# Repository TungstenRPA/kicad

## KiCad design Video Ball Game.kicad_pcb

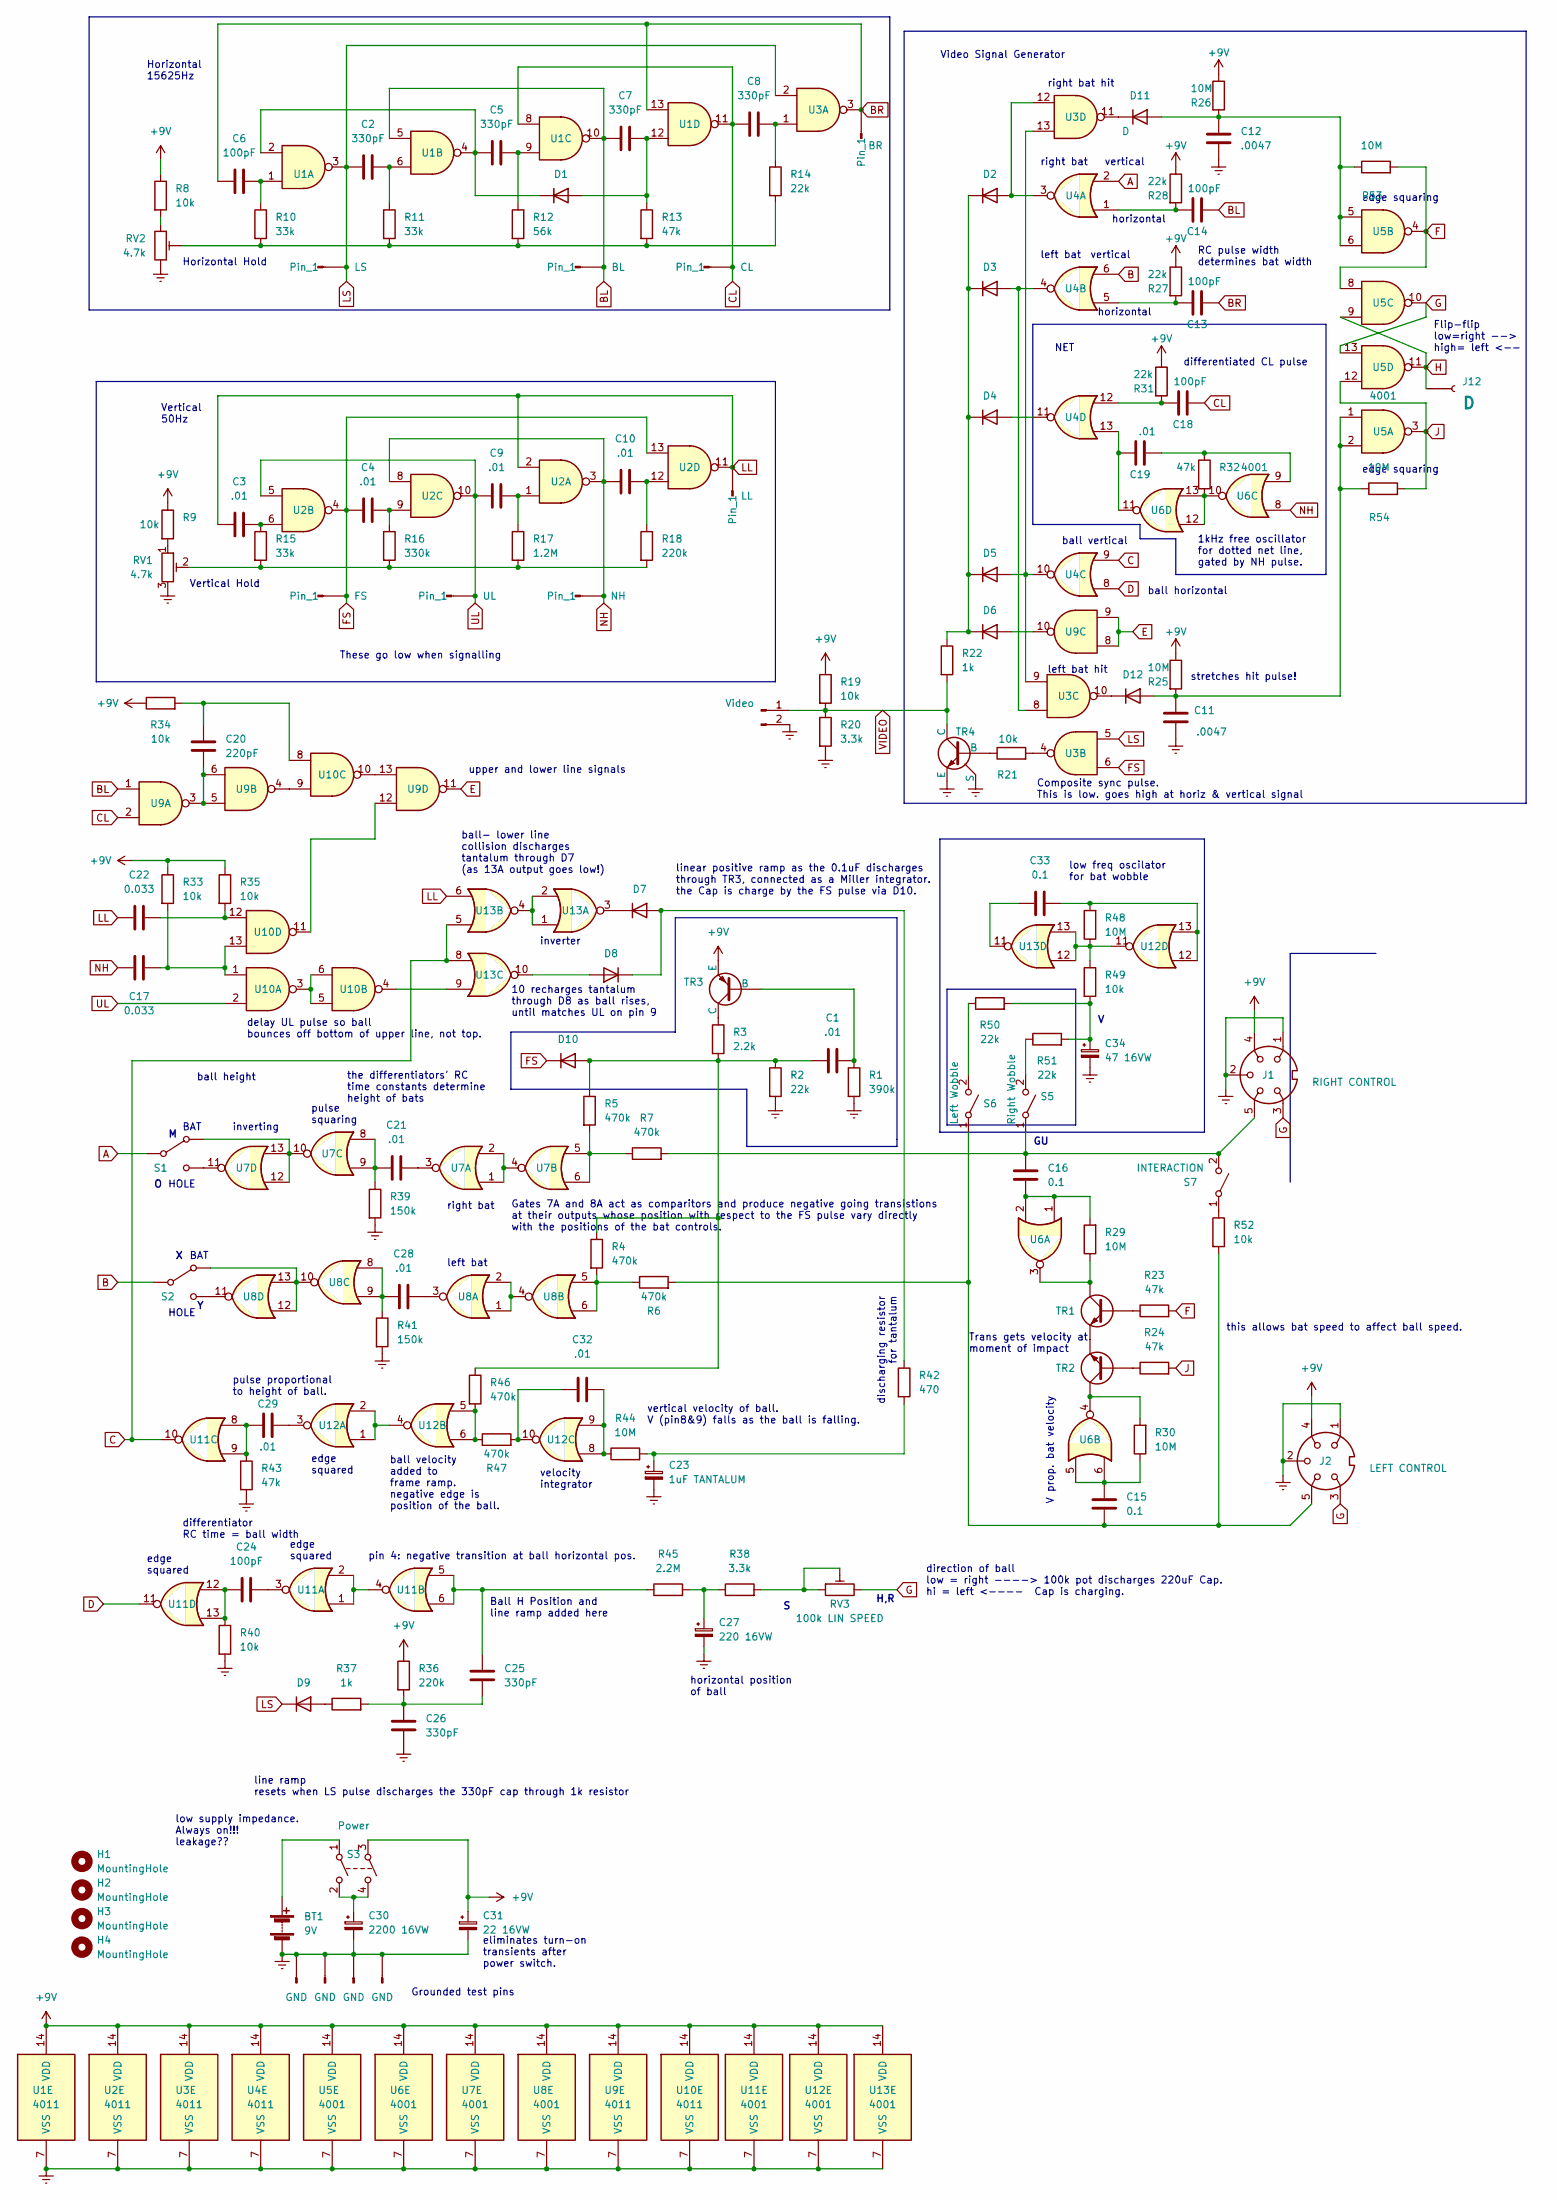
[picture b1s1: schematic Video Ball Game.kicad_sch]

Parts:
BT1: 9V; BatteryHolder_Eagle_12BH611-GR
C1, C21, C28, C29, C32: .01; C_Disc_D3.0mm_W1.6mm_P2.50mm
C2, C5, C7, C8: 330pF; C_Axial_L3.8mm_D2.6mm_P7.50mm_Horizontal
C3, C4, C9, C10, C19: .01; C_Rect_L7.2mm_W3.0mm_P5.00mm_FKS2_FKP2_MKS2_MKP2
C6, C24: 100pF; C_Disc_D3.0mm_W1.6mm_P2.50mm
C11, C12: .0047; C_Rect_L7.2mm_W3.0mm_P5.00mm_FKS2_FKP2_MKS2_MKP2
C13, C14, C18: 100pF; C_Axial_L3.8mm_D2.6mm_P7.50mm_Horizontal
C15, C16, C33: 0.1; C_Disc_D3.0mm_W1.6mm_P2.50mm
C17, C22: 0.033; C_Disc_D3.0mm_W1.6mm_P2.50mm
C20: 220pF; C_Rect_L7.2mm_W3.0mm_P5.00mm_FKS2_FKP2_MKS2_MKP2
C23: 1uF TANTALUM; C_Disc_D3.8mm_W2.6mm_P2.50mm
C25, C26: 330pF; C_Disc_D3.0mm_W1.6mm_P2.50mm
C27: 220 16VW; CP_Radial_D8.0mm_P5.00mm
C30: 2200 16VW; CP_Radial_D18.0mm_P7.50mm
C31: 22 16VW; CP_Radial_D8.0mm_P5.00mm
C34: 47 16VW; CP_Radial_D8.0mm_P5.00mm
D1, D2, D3, D4, D5, D6, D7, D8, D9, D10, D11, D12: D; D_A-405_P7.62mm_Horizontal
H1, H2, H3, H4: MountingHole; MountingHole_2.2mm_M2_ISO14580_Pad_TopBottom
J1: RIGHT CONTROL; PinHeader_1x05_P2.54mm_Vertical
J2: LEFT CONTROL; PinHeader_1x05_P2.54mm_Vertical
J3: FS; PinSocket_1x01_P2.54mm_Vertical
J4: UL; PinSocket_1x01_P2.54mm_Vertical
J5: NH; PinSocket_1x01_P2.54mm_Vertical
J6: LL; PinSocket_1x01_P2.54mm_Vertical
J7, J9, J10, J11: GND; PinSocket_1x01_P2.54mm_Vertical
J8: LS; PinSocket_1x01_P2.54mm_Vertical
J12: D; PinSocket_1x01_P2.54mm_Vertical
J13: BL; PinSocket_1x01_P2.54mm_Vertical
J14: CL; PinSocket_1x01_P2.54mm_Vertical
J15: Video; PinSocket_1x02_P2.54mm_Vertical
J16: BR; PinSocket_1x01_P2.54mm_Vertical
R1: 390k; R_Axial_DIN0204_L3.6mm_D1.6mm_P5.08mm_Horizontal
R2, R14, R27, R28, R31, R50, R51: 22k; R_Axial_DIN0204_L3.6mm_D1.6mm_P5.08mm_Horizontal
R3: 2.2k; R_Axial_DIN0204_L3.6mm_D1.6mm_P5.08mm_Horizontal
R4, R5, R6, R7, R46, R47: 470k; R_Axial_DIN0204_L3.6mm_D1.6mm_P5.08mm_Horizontal
R8, R9, R19, R21, R33, R34, R35, R40, R49, R52: 10k; R_Axial_DIN0204_L3.6mm_D1.6mm_P5.08mm_Horizontal
R10, R11, R15: 33k; R_Axial_DIN0204_L3.6mm_D1.6mm_P5.08mm_Horizontal
R12: 56k; R_Axial_DIN0204_L3.6mm_D1.6mm_P5.08mm_Horizontal
R13, R23, R24, R32, R43: 47k; R_Axial_DIN0204_L3.6mm_D1.6mm_P5.08mm_Horizontal
R16: 330k; R_Axial_DIN0204_L3.6mm_D1.6mm_P5.08mm_Horizontal
R17: 1.2M; R_Axial_DIN0204_L3.6mm_D1.6mm_P5.08mm_Horizontal
R18, R36: 220k; R_Axial_DIN0204_L3.6mm_D1.6mm_P5.08mm_Horizontal
R20, R38: 3.3k; R_Axial_DIN0204_L3.6mm_D1.6mm_P5.08mm_Horizontal
R22, R37: 1k; R_Axial_DIN0204_L3.6mm_D1.6mm_P5.08mm_Horizontal
R25, R26, R29, R30, R44, R48, R53, R54: 10M; R_Axial_DIN0204_L3.6mm_D1.6mm_P5.08mm_Horizontal
R39, R41: 150k; R_Axial_DIN0204_L3.6mm_D1.6mm_P5.08mm_Horizontal
R42: 470; R_Axial_DIN0204_L3.6mm_D1.6mm_P5.08mm_Horizontal
R45: 2.2M; R_Axial_DIN0204_L3.6mm_D1.6mm_P5.08mm_Horizontal
RV1, RV2: 4.7k; Potentiometer_Bourns_3266Y_Vertical
RV3: 100k LIN SPEED; Potentiometer_Bourns_3266Y_Vertical
S1: Right Bat/Hole; PinHeader_1x03_P2.54mm_Vertical
S2: Left Bat/Hole; PinHeader_1x03_P2.54mm_Vertical
S3: Power; PinHeader_1x03_P2.54mm_Vertical
S5: Right Wobble; PinHeader_1x02_P2.54mm_Vertical
S6: Left Wobble; PinHeader_1x02_P2.54mm_Vertical
S7: INTERACTION; PinSocket_1x02_P2.54mm_Vertical
TR1, TR2: Q_NPN_BCE; TO-92
TR3: BC558; TO-92
TR4: Q_NPN_BCES; TO-72-4
U1, U2, U3, U4, U9, U10: 4011; DIP-14_W7.62mm_Socket
U5, U6, U7, U8, U11, U12, U13: 4001; DIP-14_W7.62mm_Socket

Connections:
+9V: C31.1, J1.4, J2.4, R8.1, R9.1, R19.1, R25.1, R26.1, R27.1, R28.1, R31.1, R33.1, R34.1, R35.1, R36.1, S3.3, TR3.3 (E), U1.14 (VDD), U2.14 (VDD), U3.14 (VDD), U4.14 (VDD), U5.14 (VDD), U6.14 (VDD), U7.14 (VDD), U8.14 (VDD), U9.14 (VDD), U10.14 (VDD), U11.14 (VDD), U12.14 (VDD), U13.14 (VDD)
A: S1.2 (B), U4.2
B: S2.2 (B), U4.6
BL: C7.1, C14.2, J13.1, U1.5, U1.10, U9.1
BR: C6.1, C13.2, J16.1, U1.13, U3.3
C: U4.9, U11.10, U13.5, U13.8
CL: C8.1, C18.2, J14.1, U1.8, U1.11, U9.2
D: U4.8, U11.11
E: U9.8, U9.9, U9.11
Earth: BT1.2 (-), C11.2, C12.2, C23.2, C26.1, C27.2, C30.2, C31.2, C34.2, J1.1, J1.2, J2.1, J2.2, J7.1, J9.1, J10.1, J11.1, J15.2, R1.2, R2.2, R20.2, R39.2, R40.2, R41.2, R43.2, RV1.3, RV2.3, TR4.3 (E), TR4.4 (S), U1.7 (VSS), U2.7 (VSS), U3.7 (VSS), U4.7 (VSS), U5.7 (VSS), U6.7 (VSS), U7.7 (VSS), U8.7 (VSS), U9.7 (VSS), U10.7 (VSS), U11.7 (VSS), U12.7 (VSS), U13.7 (VSS)
F: R23.2, R53.2, U5.4, U5.8
FS: C4.1, D10.1 (K), J3.1, U2.4, U2.13, U3.6
G: J1.3, J2.3, RV3.3, U5.10, U5.13
H: J12.1, U5.9, U5.11
J: R24.2, R54.2, U5.3, U5.12
LL: C3.1, C22.1, J6.1, U2.2, U2.11, U13.6
LS: C2.1, D9.1 (K), J8.1, U1.3, U3.2, U3.5
NH: C10.1, C17.1, J5.1, U2.3, U2.8, U6.8
unnamed: BT1.1 (+), S3.1
unnamed: C1.1, D10.2 (A), R2.1, R3.2, R4.1, R5.1, R46.1
unnamed: C1.2, R1.1, TR3.2 (B)
unnamed: C2.2, R11.1, U1.6
unnamed: C3.2, R15.1, U2.6
unnamed: C4.2, R16.1, U2.9
unnamed: C5.1, D1.1 (K), U1.2, U1.4
unnamed: C5.2, R12.1, U1.9
unnamed: C6.2, R10.1, U1.1
unnamed: C7.2, D1.2 (A), R13.1, U1.12
unnamed: C8.2, R14.1, U3.1
unnamed: C9.2, R17.1, U2.1
unnamed: C10.2, R18.1, U2.12
unnamed: C11.1, D12.2 (A), R25.2, R54.1, U5.1, U5.2
unnamed: C12.1, D11.2 (A), R26.2, R53.1, U5.5, U5.6
unnamed: C13.1, R27.2, U4.5
unnamed: C14.1, R28.2, U4.1
unnamed: C15.1, J2.5, R6.2, R52.2, S6.1 (A)
unnamed: C15.2, R30.1, U6.5, U6.6
unnamed: C16.1, R29.2, U6.1, U6.2
unnamed: C16.2, J1.5, R7.2, S5.1 (A), S7.2 (B)
unnamed: C17.2, R33.2, U10.1, U10.13
unnamed: C18.1, R31.2, U4.12
unnamed: C19.1, U4.13, U6.11
unnamed: C19.2, R32.1, U6.9
unnamed: C20.1, R34.2, U10.8
unnamed: C20.2, U9.3, U9.5, U9.6
unnamed: C21.1, R39.1, U7.8, U7.9
unnamed: C21.2, U7.3
unnamed: C22.2, R35.2, U10.12
unnamed: C23.1, R42.2, R44.2
unnamed: C24.1, R40.1, U11.12, U11.13
unnamed: C24.2, U11.3
unnamed: C25.1, C26.2, R36.2, R37.2
unnamed: C25.2, R45.1, U11.5, U11.6
unnamed: C27.1, R38.1, R45.2
unnamed: C28.1, R41.1, U8.8, U8.9
unnamed: C28.2, U8.3
unnamed: C29.1, R43.1, U11.8, U11.9
unnamed: C29.2, U12.3
unnamed: C30.1, S3.2, S3.4
unnamed: C32.1, R47.2, U12.10
unnamed: C32.2, R44.1, U12.8, U12.9
unnamed: C33.1, R48.2, U12.12, U12.13
unnamed: C33.2, U13.11
unnamed: C34.1, R49.2, R50.2, R51.2
unnamed: D2.1 (K), D3.1 (K), D4.1 (K), D5.1 (K), D6.1 (K), R22.1
unnamed: D2.2 (A), U3.12, U4.3
unnamed: D3.2 (A), U3.8, U4.4
unnamed: D4.2 (A), U4.11
unnamed: D5.2 (A), U3.9, U3.13, U4.10
unnamed: D6.2 (A), U9.10
unnamed: D7.1 (K), U13.3
unnamed: D7.2 (A), D8.1 (K), R42.1
unnamed: D8.2 (A), U13.10
unnamed: D9.2 (A), R37.1
unnamed: D11.1 (K), U3.11
unnamed: D12.1 (K), U3.10
unnamed: R3.1, TR3.1 (C)
unnamed: R4.2, R6.1, U8.5, U8.6
unnamed: R5.2, R7.1, U7.5, U7.6
unnamed: R8.2, RV2.1
unnamed: R9.2, RV1.1
unnamed: R10.2, R11.2, R12.2, R13.2, R14.2, RV2.2
unnamed: R15.2, R16.2, R17.2, R18.2, RV1.2
unnamed: R21.1, TR4.1 (B)
unnamed: R21.2, U3.4
unnamed: R23.1, TR1.1 (B)
unnamed: R24.1, TR2.1 (B)
unnamed: R29.1, TR1.2 (C), U6.3
unnamed: R30.2, TR2.2 (C), U6.4
unnamed: R32.2, U6.10, U6.12, U6.13
unnamed: R38.2, RV3.1, RV3.2
unnamed: R46.2, R47.1, U12.5, U12.6
unnamed: R48.1, R49.1, U12.11, U13.12, U13.13
unnamed: R50.1, S6.2 (B)
unnamed: R51.1, S5.2 (B)
unnamed: R52.1, S7.1 (A)
unnamed: S1.1 (A), U7.10, U7.12, U7.13
unnamed: S1.3 (C), U7.11
unnamed: S2.1 (A), U8.10, U8.12, U8.13
unnamed: S2.3 (C), U8.11
unnamed: TR1.3 (E), TR2.3 (E)
unnamed: U7.1, U7.2, U7.4
unnamed: U8.1, U8.2, U8.4
unnamed: U10.3, U10.5, U10.6
unnamed: U10.4, U13.9
unnamed: U9.4, U10.9
unnamed: U9.13, U10.10
unnamed: U9.12, U10.11
unnamed: U11.1, U11.2, U11.4
unnamed: U12.1, U12.2, U12.4
unnamed: U13.1, U13.2, U13.4
UL: C9.1, J4.1, U2.5, U2.10, U10.2
VIDEO: J15.1, R19.2, R20.1, R22.2, TR4.2 (C)

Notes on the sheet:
right bat
Flip-flip low=right --> high= left <--
Horizontal Hold
stretches hit pulse!
edge squared
edge squaring
this allows bat speed to affect ball speed.
ball horizontal
ball velocity added to frame ramp. negative edge is position of the ball.
horizontal
eliminates turn-on transients after power switch.
Gates 7A and 8A act as comparitors and produce negative going transistions at their outputs whose position with respect to the FS pulse vary directly with the positions of the bat controls.
pulse proportional to height of ball.
differentiated CL pulse
HOLE
Vertical 50Hz
right bat hit
the differentiators' RC time constants determine height of bats
1kHz free oscillator for dotted net line, gated by NH pulse.
low freq oscilator for bat wobble
These go low when signalling
Composite sync pulse. This is low. goes high at horiz & vertical signal
ball height
Vertical Hold
Horizontal 15625Hz
inverting
vertical velocity of ball. V (pin8&9) falls as the ball is falling.
BAT
low supply impedance. Always on!!! leakage??
ball vertical
Trans gets velocity at moment of impact
Ball H Position and line ramp added here
line ramp resets when LS pulse discharges the 330pF cap through 1k resistor
upper and lower line signals
delay UL pulse so ball bounces off bottom of upper line, not top.
V prop. bat velocity
vertical
linear positive ramp as the 0.1uF discharges through TR3, connected as a Miller integrator. the Cap is charge by the FS pulse via D10.
inverter
H,R

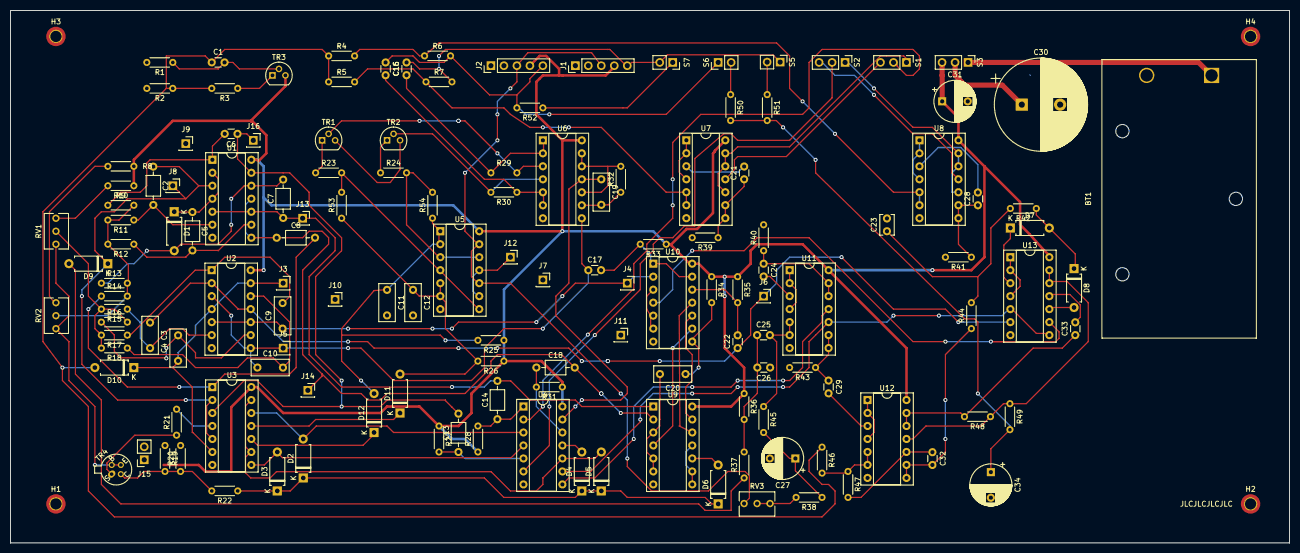
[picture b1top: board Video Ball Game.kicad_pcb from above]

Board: 2 copper layers, 250.2 x 104.1 mm, 147 parts (1 on the bottom side), 113 nets.
